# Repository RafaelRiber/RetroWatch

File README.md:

# RetroWatch
 <p align="center">
 
 <em>Front</em>
 <p align="center">
 <b>OSHPark renders</b>
 </p>
 
## Short description
A retro watch, based around the HP QDSP-6064 Bubble display, used in 70s HP calculators like the [HP-35](https://en.wikipedia.org/wiki/HP-35). The display is controlled by an Atmel ATMega328P-AU MCU with Arduino code, and the time is kept by a Maxim DS3231 Real-Time Clock module, that stays connected to the LiPo battery at all times, keeping time even when the microcontroller and display are not powered.
The code is open source, licensed under the MIT License, and the harware is fully open-source.

### Featured on:
[Hackaday.com blog post by Elliot Williams](http://hackaday.com/2016/06/25/easy-bubble-watch-oozes-retro-charm/)

[Hackaday.io project page](https://hackaday.io/project/12402-retrowatch)
  
## Hardware
### PCB
The board design was made in Eagle, has been tested and works. A 500 mAh [LiPo Battery from Adafruit](https://adafru.it/1578) fits perfectly under the board. It can be freely modified. It can also directly be ordered on the OSHPark website: 
<p align="center"><a href="https://oshpark.com/shared_projects/3zNSaolF"></img></a></p>

(DISCLAIMER: I am in no way affiliated with Atmel. I just put the Atmel logo on the PCB to show the circuit uses an Atmel chip, which I really like !)

### Bill Of Materials
You can find the BOM [here](https://github.com/RafaelRiber/RetroWatch/blob/master/BOM.md).
  
## Software
The software was written in Arduino code, is licensed under MIT License, and can be uploaded on the microcontroller via ISP.
Be sure to set the desired time in the code prior to uploading, to set the time registers on the RTC.

Functions of the code include:
* Hours, minutes and seconds
* Day, month, year, day of year, day in week, week in year.
* Stopwatch (start, stop, reset)
* Temperature reading from the real-time-clock's built-in thermometer (accurate to about 3°C)
* Brightness setting in software, saved to EEPROM to save even if the watch is powered off.
 
To be able to upload the code on the watch, an Arduno IDE board file for an "ATMega328 on a breadboard" running at 8 MHz with the internal crystal, is needed. You can find it here: https://www.arduino.cc/en/Tutorial/ArduinoToBreadboard under "Minimal Circuit (Eliminating the External Clock)"
### Required Libraries
1. [Chrono library by thomasfredericks](https://github.com/thomasfredericks/Chrono)
2. [Pushbutton library from Pololu](http://pololu.github.io/pushbutton-arduino/)
3. [RTCLib by Adafruit Industries](https://github.com/adafruit/RTClib)
4. [SevSeg by SparkFun](https://github.com/sparkfun/SevSeg)

### Planned Sofware Functions
• ~~Menu structure for mode selection~~ DONE !

• ~~Year~~ DONE !

• Time set on the watch

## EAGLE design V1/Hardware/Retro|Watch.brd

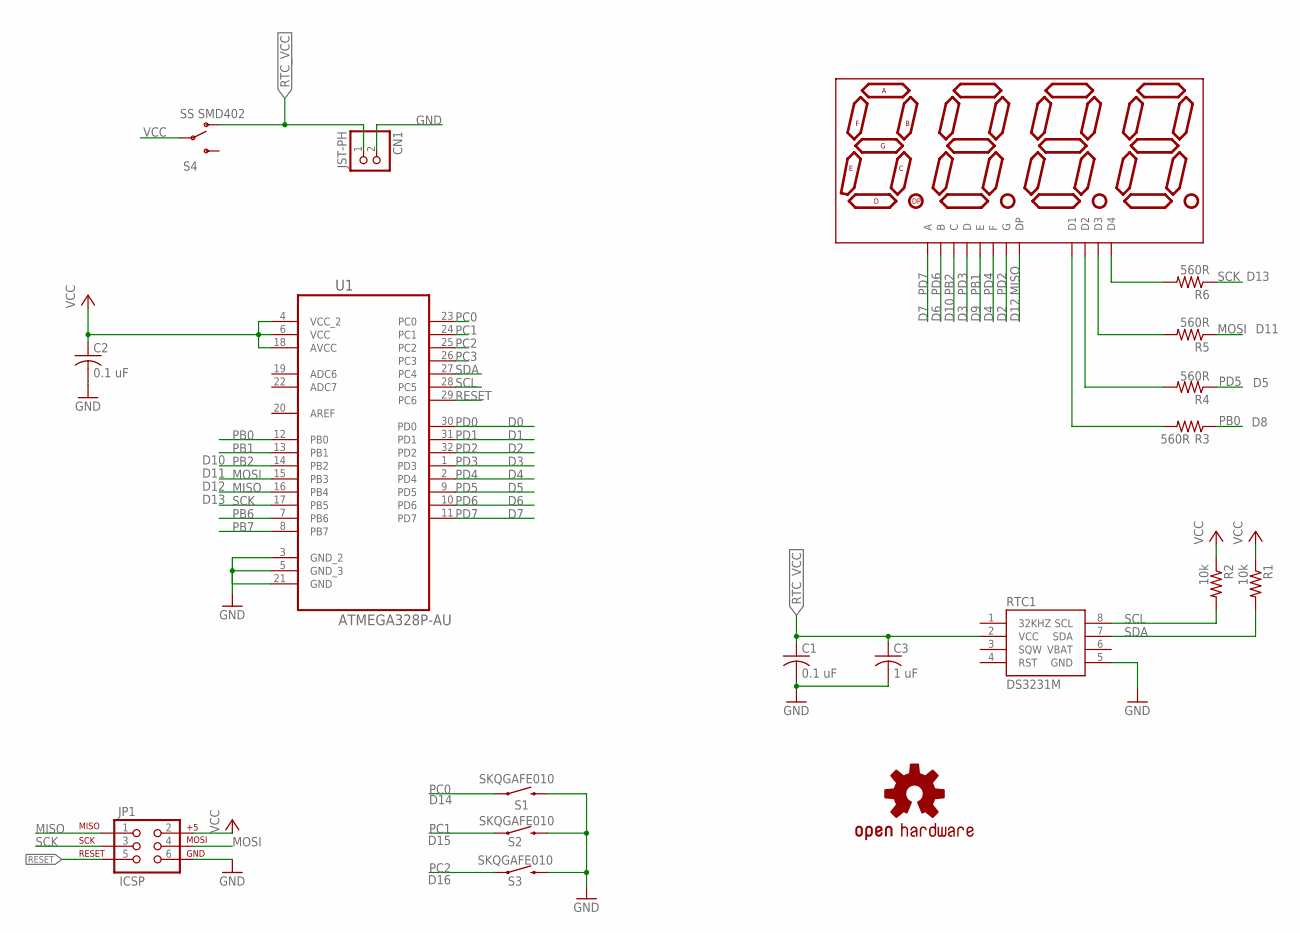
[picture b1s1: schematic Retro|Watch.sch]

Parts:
C1, C2: 0.1 uF; C0805; MPN 0805B104K500CT
C3: 1 uF; C0805
CN1: JST-PH; JST-PH-2-SMT-RA
DISP1: hp; DIL12
JP1: ICSP; 2X3_LOCK
LOGO1: OSHW-LOGOM-COPPER; OSHW-LOGO-M_COPPER
R1, R2: 10k; R0805
R3, R4, R5, R6: 560R; R0805
RTC1: DS3231M; SOIC8
S1, S2, S3: SKQGAFE010; TACTILE-SWITCH-SMD
S4: SS SMD402; SWITCH-SPDT-SMD
U1: ATMEGA328P-AU; QFP80P900X900X120-32N

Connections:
GND: C1.2, C2.2, C3.2, CN1.2 (1), JP1.6, RTC1.5 (GND), S1.3 (2), S2.3 (2), S3.3 (2), U1.3 (GND_2), U1.5 (GND_3), U1.21 (GND)
MISO: DISP1.5 (DP), JP1.1, U1.16 (PB4)
MOSI: JP1.4, R5.1, U1.15 (PB3)
unnamed: DISP1.1 (D1), R3.2
unnamed: DISP1.10 (D2), R4.2
unnamed: DISP1.4 (D3), R5.2
unnamed: DISP1.6 (D4), R6.2
PB0: R3.1, U1.12 (PB0)
PB1: DISP1.2 (E), U1.13 (PB1)
PB2: DISP1.3 (C), U1.14 (PB2)
PB6: U1.7 (PB6)
PB7: U1.8 (PB7)
PC0: S1.1, U1.23 (PC0)
PC1: S2.1, U1.24 (PC1)
PC2: S3.1, U1.25 (PC2)
PC3: U1.26 (PC3)
PD0: U1.30 (PD0)
PD1: U1.31 (PD1)
PD2: DISP1.7 (G), U1.32 (PD2)
PD3: DISP1.8 (D), U1.1 (PD3)
PD4: DISP1.9 (F), U1.2 (PD4)
PD5: R4.1, U1.9 (PD5)
PD6: DISP1.11 (B), U1.10 (PD6)
PD7: DISP1.12 (A), U1.11 (PD7)
RESET: JP1.5, U1.29 (PC6)
RTC_VCC: C1.1, C3.1, CN1.1 (2), RTC1.2 (VCC), S4.1 (O)
SCK: JP1.3, R6.1, U1.17 (PB5)
SCL: R2.2, RTC1.8 (SCL), U1.28 (PC5)
SDA: R1.2, RTC1.7 (SDA), U1.27 (PC4)
VBAT: RTC1.6 (VBAT)
VCC: C2.1, JP1.2, R1.1, R2.1, S4.2, U1.4 (VCC_2), U1.6 (VCC), U1.18 (AVCC)

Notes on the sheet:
D14
D15
D10
D11
D12
D13
D16

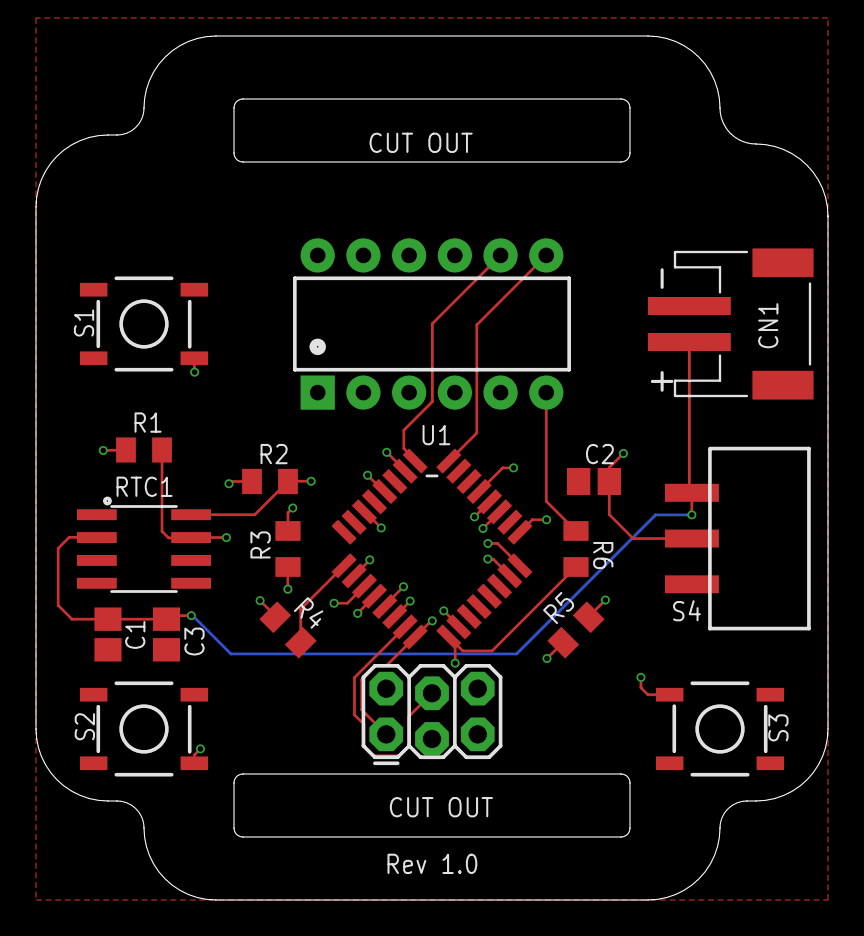
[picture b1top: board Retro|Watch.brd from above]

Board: 4 copper layers, 44.0 x 48.0 mm, 20 parts (0 on the bottom side), 25 nets.

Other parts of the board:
U$1: LOGO

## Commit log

2016-06-08 Uploaded files
2016-06-08 Uploaded file
2016-06-08 Added required libraries
2016-06-08 Restructured library folders
2016-06-08 Moved license
2016-06-08 Created README
2016-06-08 Spelling
2016-06-08 Created file
2016-06-08 Images
2016-06-08 Alignment
2016-06-08 Added image caption
2016-06-08 Corrected temperature reading
2016-06-14 Deleted files
2016-06-14 New version with stopwatch
2016-06-14 Added library list
2016-06-21 HP-35 Hyperlink
2016-06-21 Added picture
2016-06-21 Updated Retro_Watch.ino
2016-06-23 Moved in version folder
2016-06-26 Added menu structure, stopwatch reset, and a base for on-watch time set
    Added menu structure, stopwatch reset, and a base for on-watch time
    set. The last function of the menu, « Set », returns a blank screen but
    is a base for on-watch time set.
2016-06-30 Changed directory structure
2016-07-02 Updated RetroWatch.ino
    • Added day of year, day of week and week of year to date function.
    • Added brightness setting with save to EEPROM for power cycle save.
    • Added software reset function.
    • Improved menu navigation.
    • Joined hours, minutes and seconds in same function.
    • General code cleanup

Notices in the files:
parts and their libraries:
SparkFun-Displays: Licensing: Creative Commons ShareAlike 4.0 International - https://creativecommons.org/licenses/by-sa/4.0
